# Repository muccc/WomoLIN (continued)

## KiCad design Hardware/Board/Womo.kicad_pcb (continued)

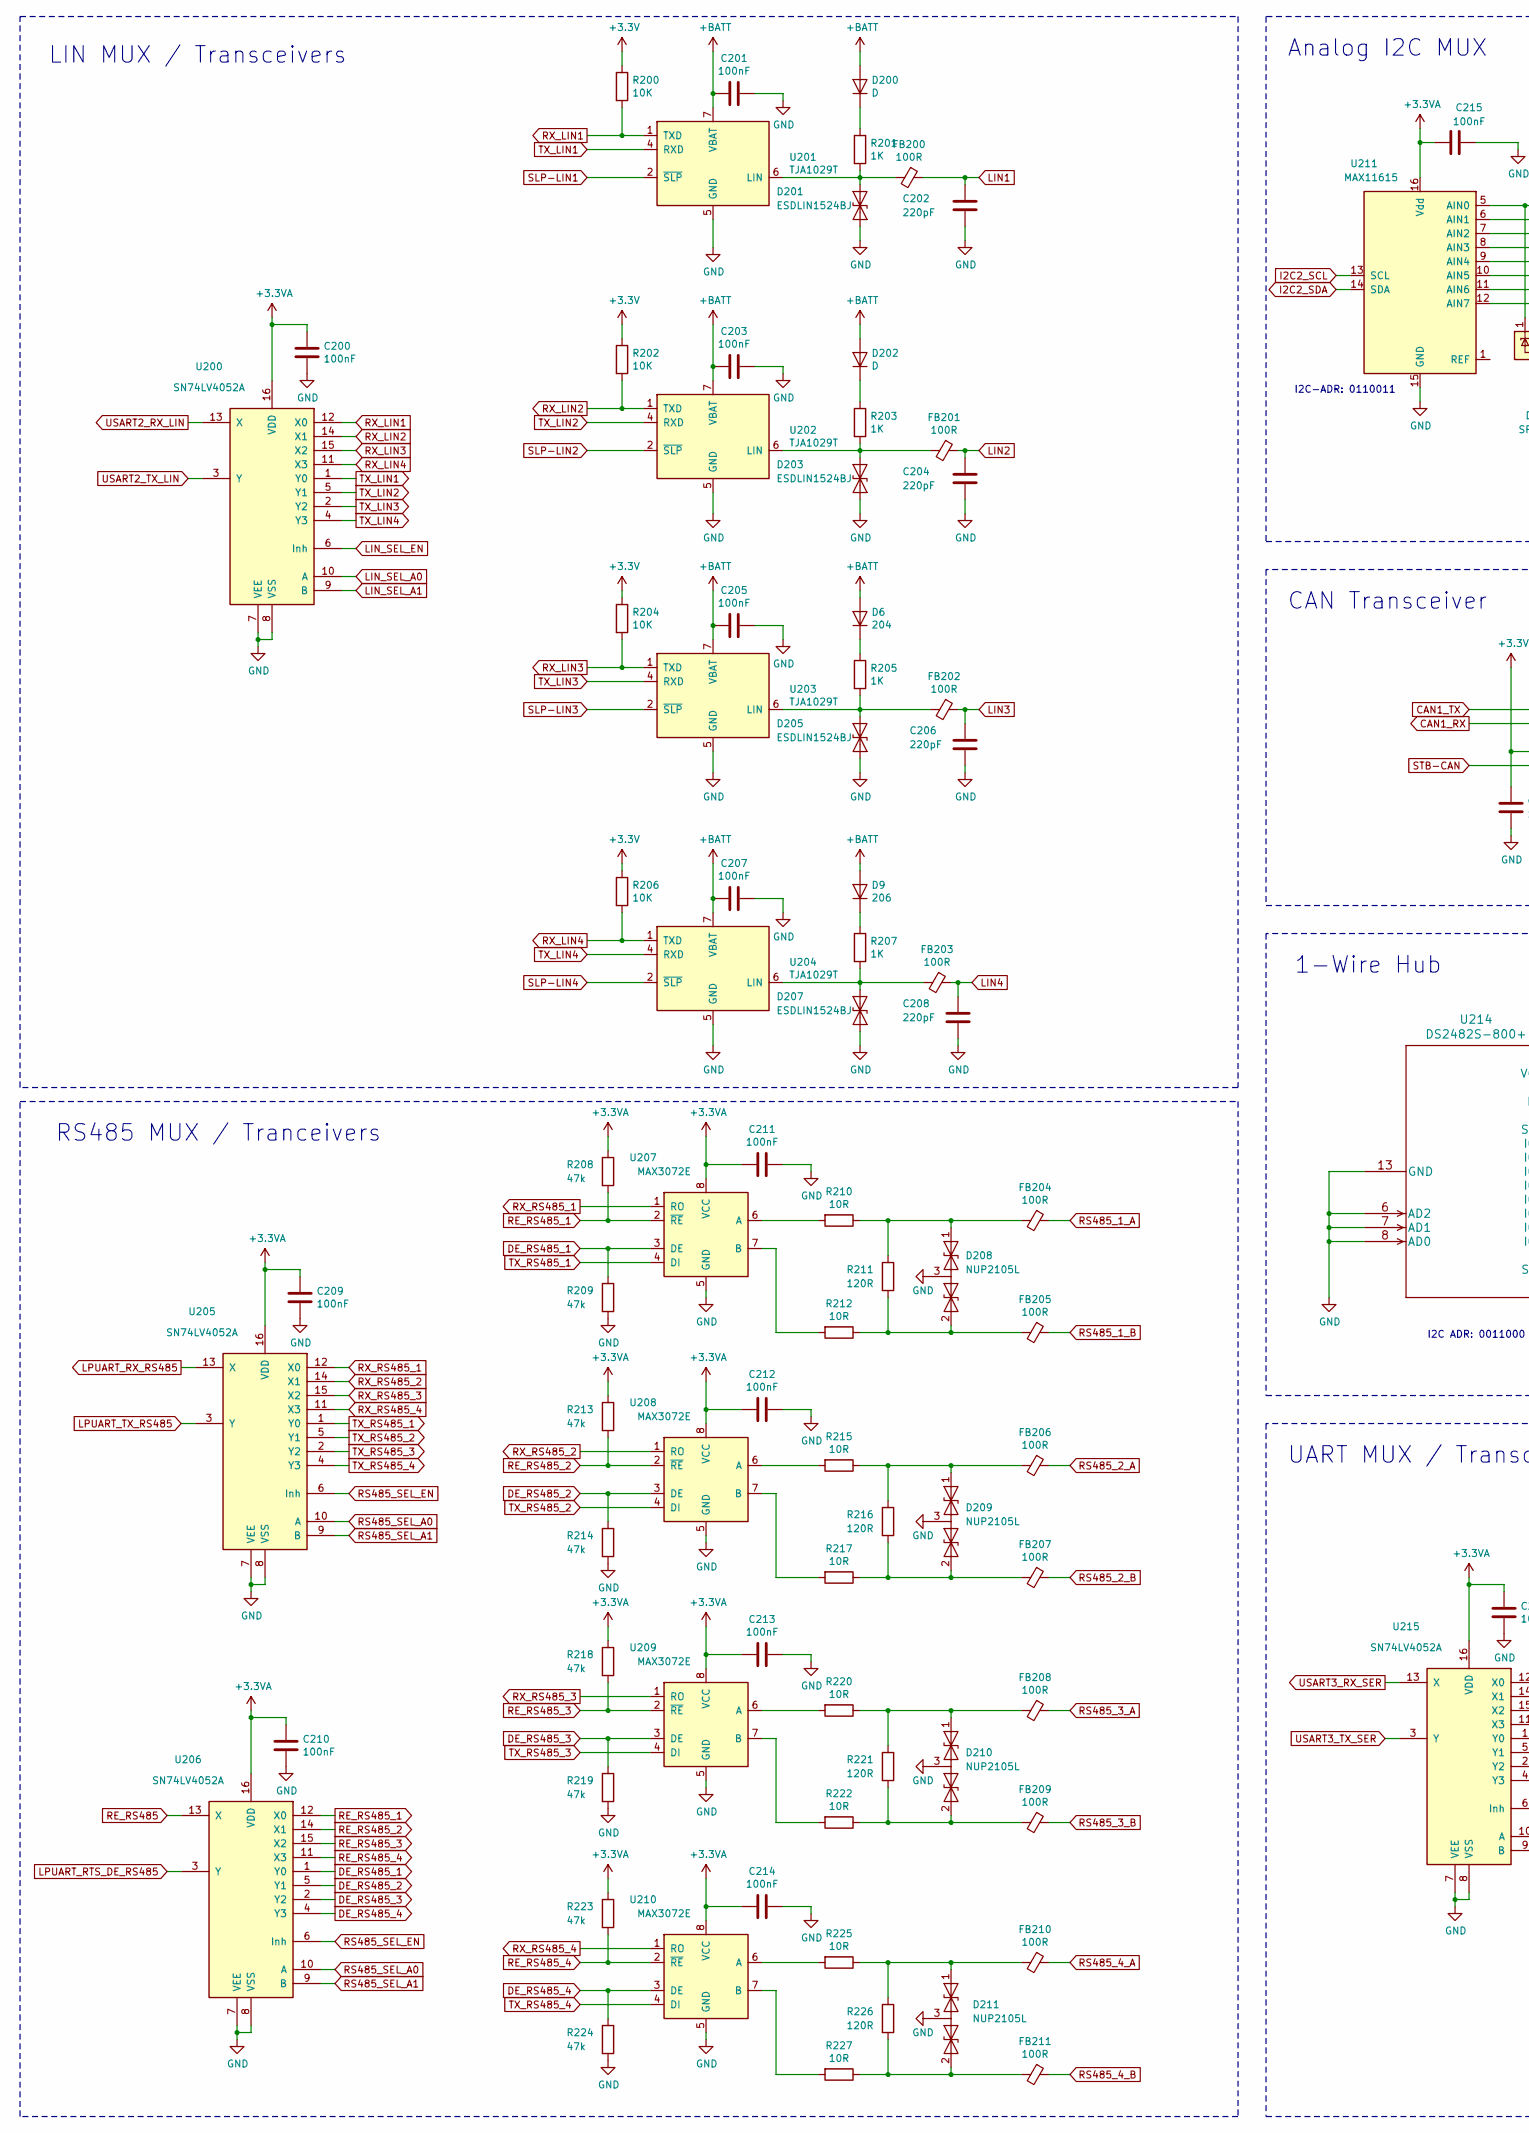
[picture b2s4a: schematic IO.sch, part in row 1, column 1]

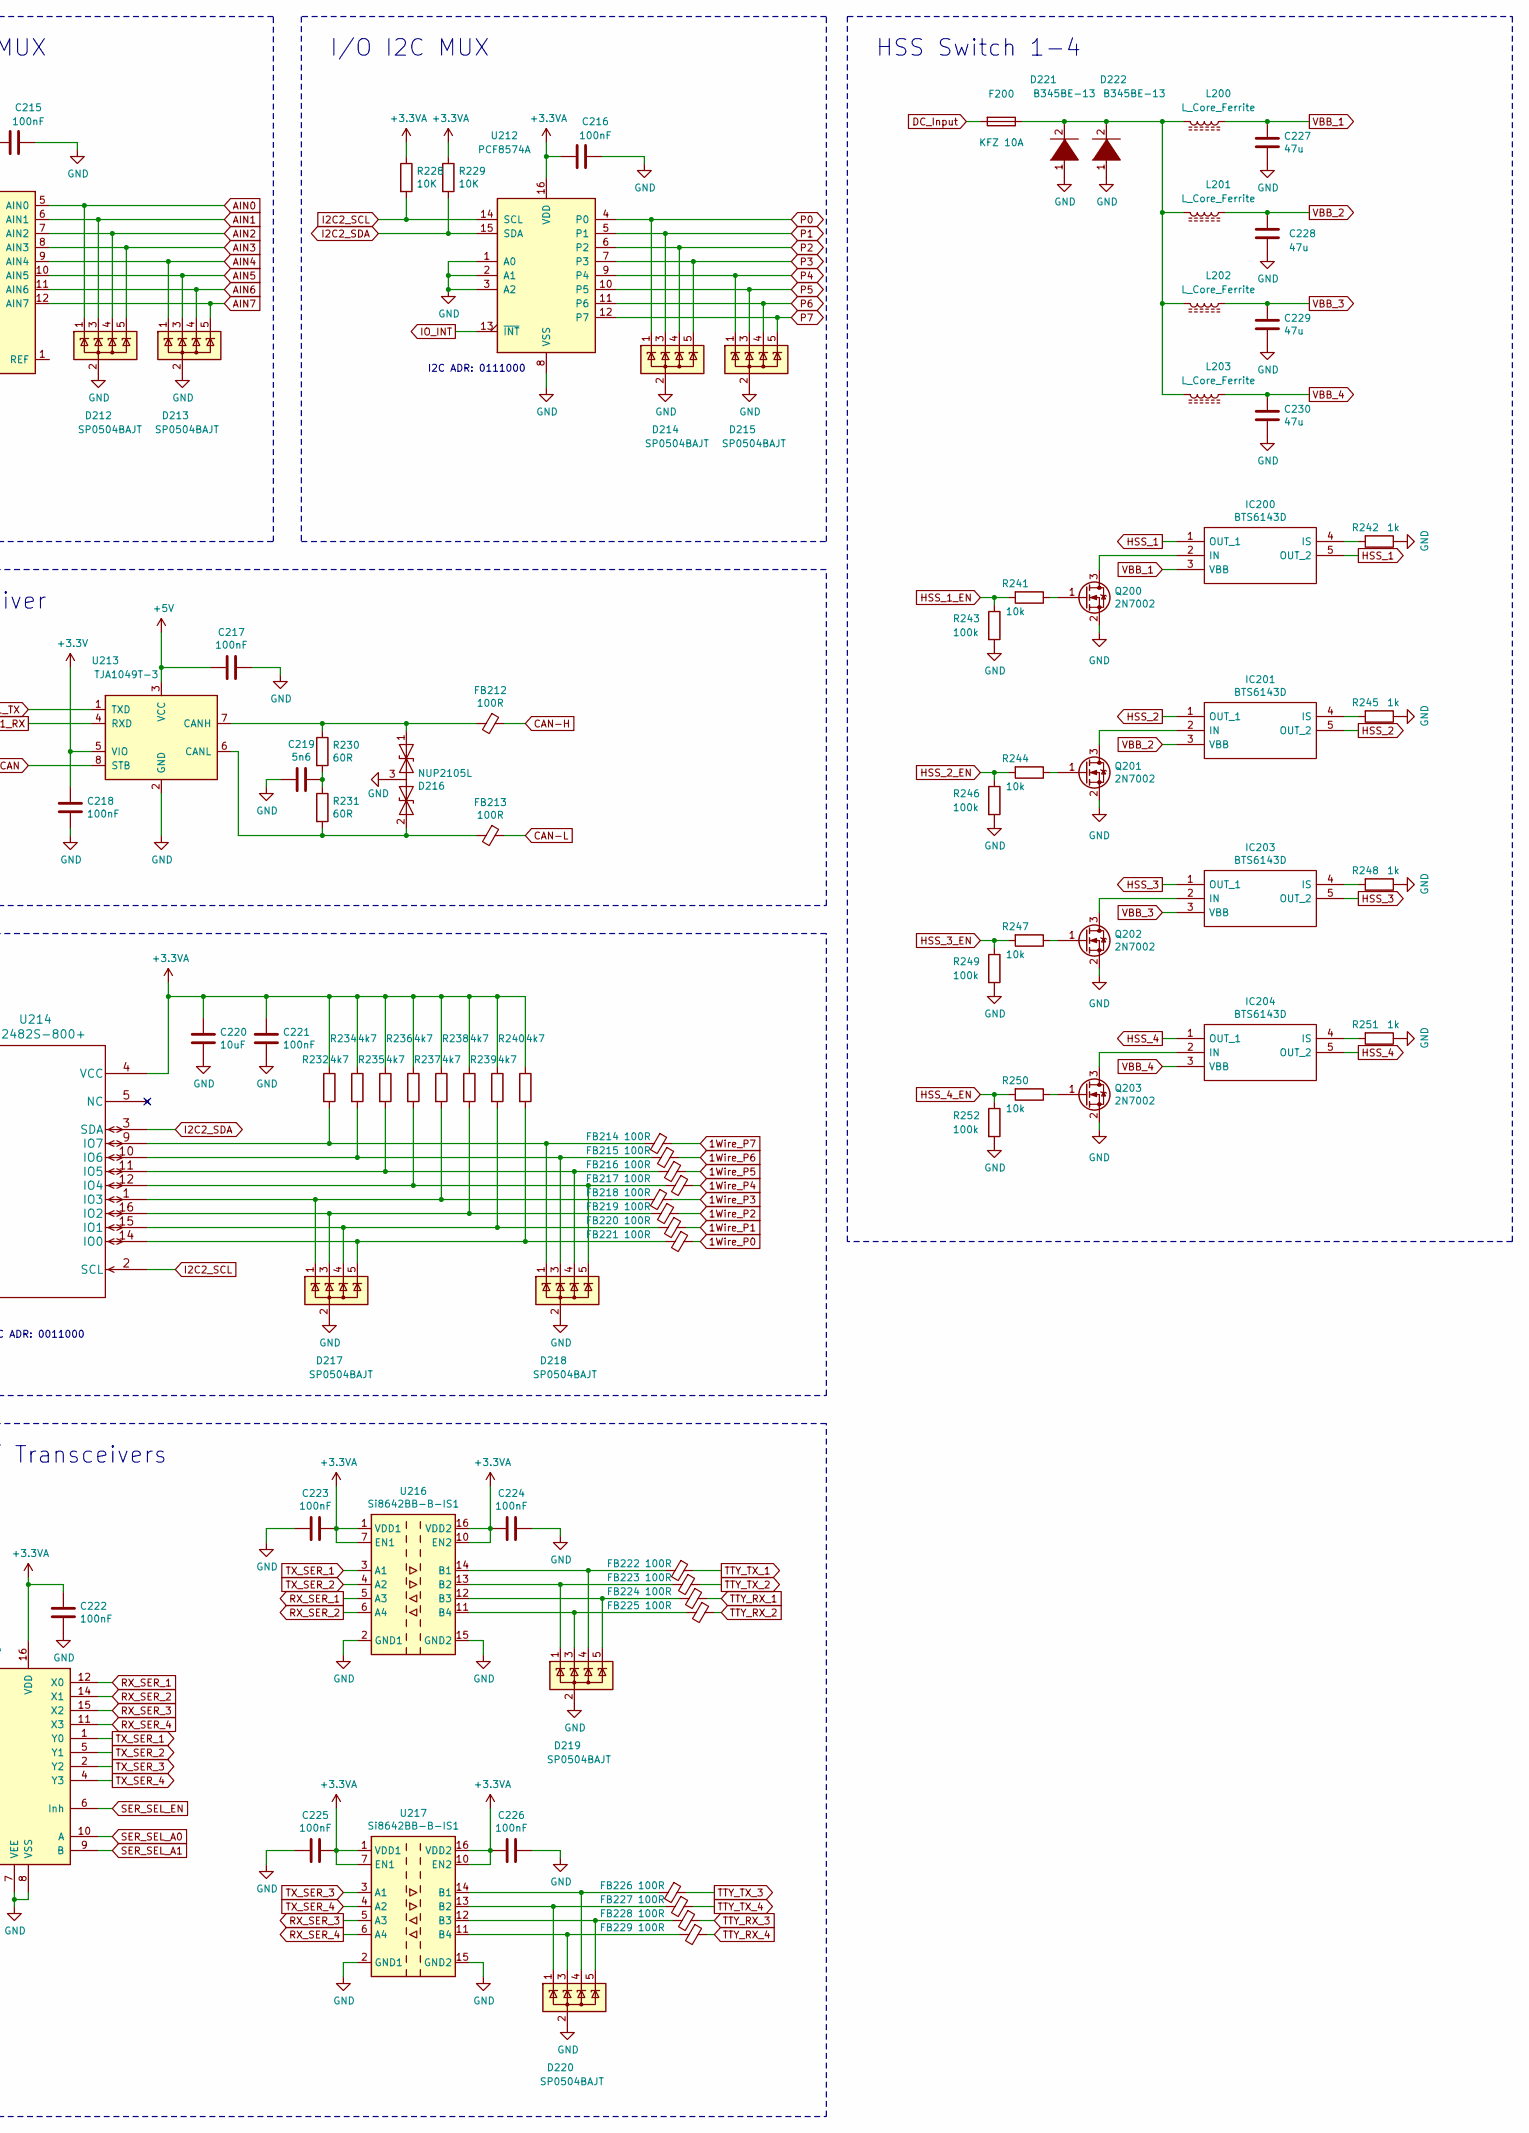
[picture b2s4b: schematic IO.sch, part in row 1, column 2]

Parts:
C200, C201, C203, C205, C207, C209, C210, C211, C212, C213, C214, C215, C216, C217, C218, C221, C222, C223, C224, C225, C226: 100nF; C_0603_1608Metric
C202, C204, C206, C208: 220pF; C_0603_1608Metric
C219: 5n6; C_0603_1608Metric
C220: 10uF; C_1210_3225Metric
C227, C228, C229, C230: 47u; C_1210_3225Metric
D6: 204; D_SOD-323
D9: 206; D_SOD-323
D200, D202: D; D_SOD-323
D201, D203, D205, D207: ESDLIN1524BJ; D_SOD-323
D208, D209, D210, D211, D216: NUP2105L; SOT-23
D212, D213, D214, D215, D217, D218, D219, D220: SP0504BAJT; SOT-353_SC-70-5
D221, D222: B345BE-13; D_SMB
F200: KFZ 10A; Fuseholder_Blade_ATO_Littelfuse_Pudenz_2_Pin
FB200, FB201, FB202, FB203, FB204, FB205, FB206, FB207, FB208, FB209, FB210, FB211, FB212, FB213, FB214, FB215, FB216, FB217, FB218, FB219, FB220, FB221, FB222, FB223, FB224, FB225, FB226, FB227, FB228, FB229: 100R; L_0603_1608Metric
IC200, IC201, IC203, IC204: BTS6143D; Mouser Part Number 726-BTS6143D
L200, L201, L202, L203: L_Core_Ferrite; L_Coilcraft_XxL4020
Q200, Q201, Q202, Q203: 2N7002; SOT-23
R200, R202, R204, R206, R228, R229: 10K; R_0603_1608Metric
R201, R203, R205, R207: 1K; R_0603_1608Metric
R208, R209, R213, R214, R218, R219, R223, R224: 47k; R_0603_1608Metric
R210, R212, R215, R217, R220, R222, R225, R227: 10R; R_0603_1608Metric
R211, R216, R221, R226: 120R; R_0603_1608Metric
R230, R231: 60R; R_0603_1608Metric
R232, R234, R235, R236, R237, R238, R239, R240: 4k7; R_0603_1608Metric
R241, R244, R247, R250: 10k; R_0603_1608Metric
R242, R245, R248, R251: 1k; R_0603_1608Metric
R243, R246, R249, R252: 100k; R_0603_1608Metric
U200, U205, U206, U215: SN74LV4052A; TSSOP-16_4.4x5mm_P0.65mm
U201, U202, U203, U204: TJA1029T; SOIC-8_3.9x4.9mm_P1.27mm
U207, U208, U209, U210: MAX3072E; SOIC-8_3.9x4.9mm_P1.27mm
U211: MAX11615; QSOP-16_3.9x4.9mm_P0.635mm
U212: PCF8574A; SOIC-16W_7.5x10.3mm_P1.27mm
U213: TJA1049T-3; SOIC-8_3.9x4.9mm_P1.27mm
U214: DS2482S-800+; SOIC-16_3.9x9.9mm_P1.27mm
U216, U217: Si8642BB-B-IS1; SOIC-16_3.9x9.9mm_P1.27mm

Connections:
1Wire_P0: FB221.1; also elsewhere on the board
1Wire_P1: FB220.1; also elsewhere on the board
1Wire_P2: FB219.1; also elsewhere on the board
1Wire_P3: FB218.1; also elsewhere on the board
1Wire_P4: FB217.1; also elsewhere on the board
1Wire_P5: FB216.1; also elsewhere on the board
1Wire_P6: FB215.1; also elsewhere on the board
1Wire_P7: FB214.1; also elsewhere on the board
+3.3VA: C200.1, C209.1, C210.1, C211.2, C212.2, C213.2, C214.2, C215.2, C216.2, C220.1, C221.1, C222.1, C223.1, C224.2, C225.1, C226.2, R208.1, R213.1, R218.1, R223.1, R228.1, R229.1, R232.1, R234.1, R235.1, R236.1, R237.1, R238.1, R239.1, R240.1, U200.16 (VDD), U205.16 (VDD), U206.16 (VDD), U207.8 (VCC), U208.8 (VCC), U209.8 (VCC), U210.8 (VCC), U211.16 (Vdd), U212.16 (VDD), U214.4 (VCC), U215.16 (VDD), U216.1 (VDD1), U216.7 (EN1), U216.10 (EN2), U216.16 (VDD2), U217.1 (VDD1), U217.7 (EN1), U217.10 (EN2), U217.16 (VDD2); also elsewhere on the board
+3V3: C218.1, R200.1, R202.1, R204.1, R206.1, U213.5 (VIO); also elsewhere on the board
+5V: C217.2, U213.3 (VCC); also elsewhere on the board
+BATT: C201.2, C203.2, C205.2, C207.2, D6.2 (A), D9.2 (A), D200.2 (A), D202.2 (A), U201.7 (VBAT), U202.7 (VBAT), U203.7 (VBAT), U204.7 (VBAT); also elsewhere on the board
AIN0: D212.1 (K), U211.5 (AIN0); also elsewhere on the board
AIN1: D212.3 (K), U211.6 (AIN1); also elsewhere on the board
AIN2: D212.4 (K), U211.7 (AIN2); also elsewhere on the board
AIN3: D212.5 (K), U211.8 (AIN3); also elsewhere on the board
AIN4: D213.1 (K), U211.9 (AIN4); also elsewhere on the board
AIN5: D213.3 (K), U211.10 (AIN5); also elsewhere on the board
AIN6: D213.4 (K), U211.11 (AIN6); also elsewhere on the board
AIN7: D213.5 (K), U211.12 (AIN7); also elsewhere on the board
CAN1_RX: U213.4 (RXD); also elsewhere on the board
CAN1_TX: U213.1 (TXD); also elsewhere on the board
CAN-H: FB212.1; also elsewhere on the board
CAN-L: FB213.1; also elsewhere on the board
DC_Input: F200.2; also elsewhere on the board
DE_RS485_1: R209.1, U206.1 (Y0), U207.3 (DE)
DE_RS485_2: R214.1, U206.5 (Y1), U208.3 (DE)
DE_RS485_3: R219.1, U206.2 (Y2), U209.3 (DE)
DE_RS485_4: R224.1, U206.4 (Y3), U210.3 (DE)
GND: C200.2, C201.1, C202.2, C203.1, C204.2, C205.1, C206.2, C207.1, C208.2, C209.2, C210.2, C211.1, C212.1, C213.1, C214.1, C215.1, C216.1, C217.1, C218.2, C219.2, C220.2, C221.2, C222.2, C223.2, C224.1, C225.2, C226.1, C227.2, C228.2, C229.2, C230.2, D201.2 (A2), D203.2 (A2), D205.2 (A2), D207.2 (A2), D208.3 (common), D209.3 (common), D210.3 (common), D211.3 (common), D212.2 (A), D213.2 (A), D214.2 (A), D215.2 (A), D216.3 (common), D217.2 (A), D218.2 (A), D219.2 (A), D220.2 (A), D221.1 (K), D222.1 (K), Q200.2 (S), Q201.2 (S), Q202.2 (S), Q203.2 (S), R209.2, R214.2, R219.2, R224.2, R242.1, R243.2, R245.1, R246.2, R248.1, R249.2, R251.1, R252.2, U200.7 (VEE), U200.8 (VSS), U201.5 (GND), U202.5 (GND), U203.5 (GND), U204.5 (GND), U205.7 (VEE), U205.8 (VSS), U206.7 (VEE), U206.8 (VSS), U207.5 (GND), U208.5 (GND), U209.5 (GND), U210.5 (GND), U211.15 (GND), U212.1 (A0), U212.2 (A1), U212.3 (A2), U212.8 (VSS), U213.2 (GND), U214.6 (AD2), U214.7 (AD1), U214.8 (AD0), U214.13 (GND), U215.7 (VEE), U215.8 (VSS), U216.2 (GND1), U216.8 (GND1), U216.9 (GND2), U216.15 (GND2), U217.2 (GND1), U217.8 (GND1), U217.9 (GND2), U217.15 (GND2); also elsewhere on the board
HSS_1: IC200.1 (OUT_1), IC200.5 (OUT_2); also elsewhere on the board
HSS_1_EN: R241.2, R243.1; also elsewhere on the board
HSS_2: IC201.1 (OUT_1), IC201.5 (OUT_2); also elsewhere on the board
HSS_2_EN: R244.2, R246.1; also elsewhere on the board
HSS_3: IC203.1 (OUT_1), IC203.5 (OUT_2); also elsewhere on the board
HSS_3_EN: R247.2, R249.1; also elsewhere on the board
HSS_4: IC204.1 (OUT_1), IC204.5 (OUT_2); also elsewhere on the board
HSS_4_EN: R250.2, R252.1; also elsewhere on the board
I2C2_SCL: R228.2, U211.13 (SCL), U212.14 (SCL), U214.2 (SCL); also elsewhere on the board
I2C2_SDA: R229.2, U211.14 (SDA), U212.15 (SDA), U214.3 (SDA); also elsewhere on the board
IO_INT: U212.13 (~INT~); also elsewhere on the board
LIN1: C202.1, FB200.1; also elsewhere on the board
LIN2: C204.1, FB201.1; also elsewhere on the board
LIN3: C206.1, FB202.1; also elsewhere on the board
LIN4: C208.1, FB203.1; also elsewhere on the board
LIN_SEL_A0: U200.10 (A); also elsewhere on the board
LIN_SEL_A1: U200.9 (B); also elsewhere on the board
LIN_SEL_EN: U200.6 (Inh); also elsewhere on the board
LPUART_RTS_DE_RS485: U206.3 (Y); also elsewhere on the board
LPUART_RX_RS485: U205.13 (X); also elsewhere on the board
LPUART_TX_RS485: U205.3 (Y); also elsewhere on the board
unnamed: C219.1, R230.2, R231.1
unnamed: D6.1 (K), R205.1
unnamed: D9.1 (K), R207.1
unnamed: D200.1 (K), R201.1
unnamed: D201.1 (A1), FB200.2, R201.2, U201.6 (LIN)
unnamed: D202.1 (K), R203.1
unnamed: D203.1 (A1), FB201.2, R203.2, U202.6 (LIN)
unnamed: D205.1 (A1), FB202.2, R205.2, U203.6 (LIN)
unnamed: D207.1 (A1), FB203.2, R207.2, U204.6 (LIN)
unnamed: D208.1 (A1), FB204.2, R210.1, R211.1
unnamed: D208.2 (A2), FB205.2, R211.2, R212.1
unnamed: D209.1 (A1), FB206.2, R215.1, R216.1
unnamed: D209.2 (A2), FB207.2, R216.2, R217.1
unnamed: D210.1 (A1), FB208.2, R220.1, R221.1
unnamed: D210.2 (A2), FB209.2, R221.2, R222.1
unnamed: D211.1 (A1), FB210.2, R225.1, R226.1
unnamed: D211.2 (A2), FB211.2, R226.2, R227.1
unnamed: D216.1 (A1), FB212.2, R230.1, U213.7 (CANH)
unnamed: D216.2 (A2), FB213.2, R231.2, U213.6 (CANL)
unnamed: D217.1 (K), FB218.2, R237.2, U214.1 (IO3)
unnamed: D217.3 (K), FB219.2, R238.2, U214.16 (IO2)
unnamed: D217.4 (K), FB220.2, R239.2, U214.15 (IO1)
unnamed: D217.5 (K), FB221.2, R240.2, U214.14 (IO0)
unnamed: D218.1 (K), FB214.2, R232.2, U214.9 (IO7)
unnamed: D218.3 (K), FB215.2, R234.2, U214.10 (IO6)
unnamed: D218.4 (K), FB216.2, R235.2, U214.11 (IO5)
unnamed: D218.5 (K), FB217.2, R236.2, U214.12 (IO4)
unnamed: D219.1 (K), FB223.2, U216.13 (B2)
unnamed: D219.3 (K), FB225.2, U216.11 (B4)
unnamed: D219.4 (K), FB222.2, U216.14 (B1)
unnamed: D219.5 (K), FB224.2, U216.12 (B3)
unnamed: D220.1 (K), FB227.2, U217.13 (B2)
unnamed: D220.3 (K), FB229.2, U217.11 (B4)
unnamed: D220.4 (K), FB226.2, U217.14 (B1)
unnamed: D220.5 (K), FB228.2, U217.12 (B3)
unnamed: D221.2 (A), D222.2 (A), F200.1, L200.2, L201.2, L202.2, L203.2
unnamed: IC200.2 (IN), Q200.3 (D)
unnamed: IC200.4 (IS), R242.2
unnamed: IC201.2 (IN), Q201.3 (D)
unnamed: IC201.4 (IS), R245.2
unnamed: IC203.2 (IN), Q202.3 (D)
unnamed: IC203.4 (IS), R248.2
unnamed: IC204.2 (IN), Q203.3 (D)
unnamed: IC204.4 (IS), R251.2
unnamed: Q200.1 (G), R241.1
unnamed: Q201.1 (G), R244.1
unnamed: Q202.1 (G), R247.1
unnamed: Q203.1 (G), R250.1
unnamed: R210.2, U207.6 (A)
unnamed: R212.2, U207.7 (B)
unnamed: R215.2, U208.6 (A)
unnamed: R217.2, U208.7 (B)
unnamed: R220.2, U209.6 (A)
unnamed: R222.2, U209.7 (B)
unnamed: R225.2, U210.6 (A)
unnamed: R227.2, U210.7 (B)
P0: D214.1 (K), U212.4 (P0); also elsewhere on the board
P1: D214.3 (K), U212.5 (P1); also elsewhere on the board
P2: D214.4 (K), U212.6 (P2); also elsewhere on the board
P3: D214.5 (K), U212.7 (P3); also elsewhere on the board
P4: D215.1 (K), U212.9 (P4); also elsewhere on the board
P5: D215.3 (K), U212.10 (P5); also elsewhere on the board
P6: D215.4 (K), U212.11 (P6); also elsewhere on the board
P7: D215.5 (K), U212.12 (P7); also elsewhere on the board
RE_RS485: U206.13 (X); also elsewhere on the board
RE_RS485_1: R208.2, U206.12 (X0), U207.2 (~RE~)
RE_RS485_2: R213.2, U206.14 (X1), U208.2 (~RE~)
RE_RS485_3: R218.2, U206.15 (X2), U209.2 (~RE~)
RE_RS485_4: R223.2, U206.11 (X3), U210.2 (~RE~)
RS485_1_A: FB204.1; also elsewhere on the board
RS485_1_B: FB205.1; also elsewhere on the board
RS485_2_A: FB206.1; also elsewhere on the board
RS485_2_B: FB207.1; also elsewhere on the board
RS485_3_A: FB208.1; also elsewhere on the board
RS485_3_B: FB209.1; also elsewhere on the board
RS485_4_A: FB210.1; also elsewhere on the board
RS485_4_B: FB211.1; also elsewhere on the board
RS485_SEL_A0: U205.10 (A), U206.10 (A); also elsewhere on the board
RS485_SEL_A1: U205.9 (B), U206.9 (B); also elsewhere on the board
RS485_SEL_EN: U205.6 (Inh), U206.6 (Inh); also elsewhere on the board
RX_LIN1: R200.2, U200.12 (X0), U201.1 (TXD)
RX_LIN2: R202.2, U200.14 (X1), U202.1 (TXD)
RX_LIN3: R204.2, U200.15 (X2), U203.1 (TXD)
RX_LIN4: R206.2, U200.11 (X3), U204.1 (TXD)
RX_RS485_1: U205.12 (X0), U207.1 (RO)
RX_RS485_2: U205.14 (X1), U208.1 (RO)
RX_RS485_3: U205.15 (X2), U209.1 (RO)
RX_RS485_4: U205.11 (X3), U210.1 (RO)
RX_SER_1: U215.12 (X0), U216.5 (A3)
RX_SER_2: U215.14 (X1), U216.6 (A4)
RX_SER_3: U215.15 (X2), U217.5 (A3)
RX_SER_4: U215.11 (X3), U217.6 (A4)
SER_SEL_A0: U215.10 (A); also elsewhere on the board
SER_SEL_A1: U215.9 (B); also elsewhere on the board
SER_SEL_EN: U215.6 (Inh); also elsewhere on the board
SLP-LIN1: U201.2 (~SLP~); also elsewhere on the board
SLP-LIN2: U202.2 (~SLP~); also elsewhere on the board
SLP-LIN3: U203.2 (~SLP~); also elsewhere on the board
SLP-LIN4: U204.2 (~SLP~); also elsewhere on the board
STB-CAN: U213.8 (STB); also elsewhere on the board
TTY_RX_1: FB224.1; also elsewhere on the board
TTY_RX_2: FB225.1; also elsewhere on the board
TTY_RX_3: FB228.1; also elsewhere on the board
TTY_RX_4: FB229.1; also elsewhere on the board
TTY_TX_1: FB222.1; also elsewhere on the board
TTY_TX_2: FB223.1; also elsewhere on the board
TTY_TX_3: FB226.1; also elsewhere on the board
TTY_TX_4: FB227.1; also elsewhere on the board
TX_LIN1: U200.1 (Y0), U201.4 (RXD)
TX_LIN2: U200.5 (Y1), U202.4 (RXD)
TX_LIN3: U200.2 (Y2), U203.4 (RXD)
TX_LIN4: U200.4 (Y3), U204.4 (RXD)
TX_RS485_1: U205.1 (Y0), U207.4 (DI)
TX_RS485_2: U205.5 (Y1), U208.4 (DI)
TX_RS485_3: U205.2 (Y2), U209.4 (DI)
TX_RS485_4: U205.4 (Y3), U210.4 (DI)
TX_SER_1: U215.1 (Y0), U216.3 (A1)
TX_SER_2: U215.5 (Y1), U216.4 (A2)
TX_SER_3: U215.2 (Y2), U217.3 (A1)
TX_SER_4: U215.4 (Y3), U217.4 (A2)
USART2_RX_LIN: U200.13 (X); also elsewhere on the board
USART2_TX_LIN: U200.3 (Y); also elsewhere on the board
USART3_RX_SER: U215.13 (X); also elsewhere on the board
USART3_TX_SER: U215.3 (Y); also elsewhere on the board
VBB_1: C227.1, IC200.3 (VBB), L200.1
VBB_2: C228.1, IC201.3 (VBB), L201.1
VBB_3: C229.1, IC203.3 (VBB), L202.1
VBB_4: C230.1, IC204.3 (VBB), L203.1

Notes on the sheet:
I2C-ADR: 0110011
I2C ADR: 0111000
I2C ADR: 0011000
LIN MUX / Transceivers
RS485 MUX / Tranceivers
UART MUX / Transceivers
CAN Transceiver
1-Wire Hub
Analog I2C MUX
I/O I2C MUX
HSS Switch 1-4

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
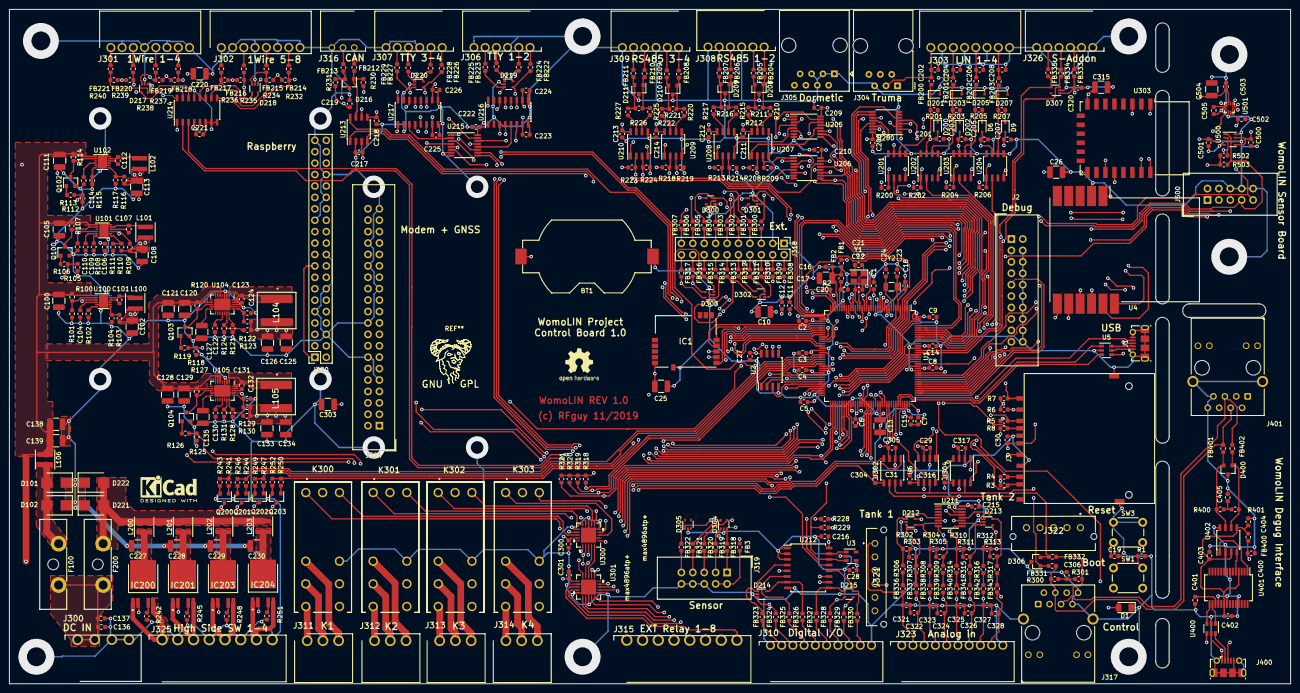
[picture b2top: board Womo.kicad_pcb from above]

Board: 4 copper layers, 285.0 x 150.0 mm, 465 parts (0 on the bottom side), 417 nets.

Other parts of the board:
C132: 100nF; C_0603_1608Metric
C133, C134: 22uF; C_1210_3225Metric
C135: 10u; C_1210_3225Metric
C136: 100n; C_0603_1608Metric
C137: 1u; C_0603_1608Metric
C138, C139: 47u; C_1210_3225Metric
F100: KFZ 5A; Fuseholder_Blade_ATO_Littelfuse_Pudenz_2_Pin
L106: L_Core_Ferrite; L_Coilcraft_XxL4020
Q104: 2N7002; SOT-23
R116: 86k6; R_0603_1608Metric
R117: 32k4; R_0603_1608Metric
R118, R125: 100k; R_0603_1608Metric
R126: 10k; R_0603_1608Metric
R127: 40k2; R_0603_1608Metric
R128: 49k9; R_0603_1608Metric
R129: 4r7; R_0603_1608Metric
R130: 105k; R_0603_1608Metric
R131: 22k6; R_0603_1608Metric
U105: MAX17574; QFN-24-1EP_4x5mm_P0.5mm_EP2.65x3.65mm

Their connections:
5V_GSM_EN: R125.1, R126.2; also elsewhere on the board
5V_Raspi_EN: R118.1; also elsewhere on the board
+3.3VA: R116.1; also elsewhere on the board
+5VL: C133.1, C134.1, R129.1, R130.1; also elsewhere on the board
+BATT: C138.1, C139.1, L106.1, R127.1, U105.5, U105.6, U105.7, U105.9; also elsewhere on the board
DC_Input: C136.1, C137.1, F100.2; also elsewhere on the board
GND: C132.2, C133.2, C134.2, C135.1, C136.2, C137.2, C138.2, C139.2, Q104.2, R117.2, R118.2, R125.2, R128.2, R131.2, U105.2, U105.3, U105.11, U105.21, U105.25; also elsewhere on the board
unnamed 125: U105.16; also elsewhere on the board
unnamed 126: U105.1, U105.23, U105.24; also elsewhere on the board
unnamed 127: U105.22; also elsewhere on the board
unnamed: C132.1, R129.2, U105.20
unnamed: C135.2, U105.12
unnamed 148: F100.1, L106.2; also elsewhere on the board
unnamed: Q104.1, R126.1
unnamed: Q104.3, R127.2, U105.10
unnamed 346: R116.2, R117.1; also elsewhere on the board
unnamed: R128.1, U105.19
unnamed: R130.2, R131.1, U105.18

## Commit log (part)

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2018-10-13 Create Log Truma CP Plus init mit AC
    Log file mit Truma CP Plus Bedienteil was init mit AC Aventis pro macht
2018-10-13 Create Log Truma CP Plus init mit Combi 6
    Truma CP Plus Bedienteil was Init mit der Compi 6 Heizung macht
2018-10-13 Create Log Truma CP Plus init mit Combi 6 und AC
    Log File init mit Bedienteil Truma CP plus, einer einer Combi 6 und Aventis pro AC, viel Trafic hinterher
2018-10-31 Update Log Truma CP Plus init mit AC
    Add Speed and Bus TIN Port
2018-10-31 Update Log Truma CP Plus init mit Combi 6
2018-10-31 Update Log Truma CP Plus init mit Combi 6 und AC
2018-10-31 Update README.md
    Warnung ins Readme
2018-10-31 Update README.md
    Anschluss Info hinzu
2019-02-17 add logs
2019-03-15 KiCad Schematic angelegt, Prozessor und Interface Bausteine ausgewählt.
2019-03-27 Businterface Schaltplan und Datasheets hinzu gefügt
2019-03-29 Controller auf 100 Pin Version geändert, Pins ersten Funktionen zugeordnet.
2019-04-01 JTAG und USB Anschlüsse zugefügt
2019-04-04 Schaltregler Design fertig gestellt, Datenblätter hinzu gefügt.
2019-04-05 FTDI EVE Touch hinzugefügt
2019-04-12 1Wire Power Pull Up. ESP Modul added
2019-04-16 Wago und FPC Libs zugefügt
2019-04-17 Netzliste und Board erstellt, hier sind noch Fehler im Bereich Footprints, BLE Modul nRF8001 hinzugefügt, erste Anschlussklemmen zugefügt
2019-04-22 Easterhegg Vortrag hinzu gefügt
2019-04-26 Änderung CPU auf einen mit Display Controller, vorbereitung zum Anschluss SSD1963 und Digital RGB Displays
2019-05-10 Display auf 40 Pin FPC reduziert, nur Verwendung des internen Display Controllers, Library Updates
2019-05-28 Octo SPI Flash und RAM zugefügt, weitere Bezeichnungen auf Stand gebracht
2019-05-31 Eine Menge Arbeit auf der GPN, fast fertig im Schaltplan.
2019-05-31 GPN Arbeit
2019-06-11 Board to Board Verbindung eingefügt
2019-06-12 Resitiven Touch Controller eingefügt, diverse I2C Parts hinzu gefügt, Netze umgenannt
2019-06-13 GSM Modul SIM800L eingefügt, Spannung MCU Board umgenannt
2019-06-14 MCU Section fertig, Analog Inputs angelegt, Schaltplan neu organisiert, alte Datenblätter entfernt.
2019-06-27 Trennung MCU und Rest, Footprints fast alles zugewiesen, GSM Modul integriert, viel Kleinkram
2019-06-28 Footprints zuweisungen
2019-07-02 Alle Footprints definiert, Libs angepasst, Layout gestartet mit Plazierung, Controller und Breakout Netzmäßig getrennt.
2019-07-03 Komplete enummerierung Geändert, Schaltplan zusammengefasst, Layout nochmals reset. BOM zu 75% fertig gestellt
2019-07-05 BOM für Mouser fertig gestellt.
2019-07-11 Bauteil Gruppierungen im Layout
2019-09-19 Änderung des Konzeptes auf 2 Boards, eines TFT Touch mit STM32L4R9, das rein die Bedienung macht. Control Board mit STM32L476, mit noch mehr Schnittstellen. Bus zwischen Display, Board, Raspberry/ESP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
2019-09-19 added system applikation und benutzerschnittstellen jeweils version 1.0
2019-09-19 added gui display unit freeplan
2019-09-22 added dia hardware-controlbus version 1.0
2019-09-26 Display Unit Lib Fehler behoben, und noch Zeug raus geworfen Library jetzt projekt spezifisch im Hardware root.. Hauptplatine rund um den Prozessor a bissl was getan, vorbereitung Quadspi Flash und S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
2019-09-27 Alle Busse aus dem Prozessor geroutet, Multplexing der LIN, RS485 und TTY Busse, diverse Aufräumarbeiten.
2019-09-28 added first pc gui
2019-10-01 Prozessor Pins zugeordnet, 4 bistabile Relais, CAN Control Interface, CAN Debug Adapter, Lagesensor zugefügt, Umwelt Sensor, ISM 868 MHz Tranceiver, ESP and Control Bus. UID Eprom. Etliche Aufräum Ar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
2019-10-02 Lib Update, Relais Treiber hinzugefügt, Kleinkram
2019-10-02 Vorher Speichern hilft
2019-10-03 added signals.xml
2019-10-04 Wago Steckverbinder hinzugefügt, Schaltplan erheblich aufgeräumt, Funktionsgruppen bezeichnet, Extension Port (Port PF) als Stecker hinzu gefügt
2019-10-04 added first version of Readme and Dockerfile
2019-10-04 test add image to readme
2019-10-04 test image to readme
2019-10-04 added image benutzerschnittstellen to readme and test link to latest
2019-10-04 image link dont work within readme
2019-10-05 Dockerfile modified
2019-10-06 docker stuff and renamend doc to Doc
2019-10-06 docker stuff added kicad to docker
2019-10-08 modified README
2019-10-08 added xml units
2019-10-14 Schaltplan erst mal fertig gestellt, Bilblotheken angepasst, High Side Treiber zugefügt
2019-10-15 added Projektbeschreibung
2019-10-16 Schaltplan: Pulldown bei den Mosfets zugefügt, Fehler Korrektur, Baulteil Footprints zugewiesen und Lib angepasst, Netztliste ohne Fehler zum Layout übertragbar. Board: Auf neues Design angepasst, Be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
2019-10-17 Schaltplan: Kleinere Korrekturen Layout: I/O Ports Gröstenteils platziert
2019-10-18 Grobplatzierung abgeschlossen, Raspberry und GSM/GNSS Bohrungen Platziert, Befestigungsbohrungen festgelegt, Board Outline festgelegt
2019-10-19 Hardware Beschreibung ergänzt
2019-10-22 added docker for gcc 9
2019-10-24 added docker openjre11
2019-10-24 added docker eclipse
2019-10-27 added dockerfiles and myfr test programm
2019-10-27 docker stuff, add ignore for dot files and little changes on myfr test software
2019-10-27 added first version of uml diagram for sigunits, modified myfr test main
2019-10-28 Daten für Vortrag 36c3 ergänzt
2019-11-01 backup myfr stuff
2019-11-01 added myfr first prj structure
2019-11-01 added myfr readme file, added unittest in cmake file
2019-11-01 added birelay software design
2019-11-06 Kleinkram Layout
2019-11-12 Layout Arbeit, Project Library sollte jetzt auf allen Rechnern funktionieren. Leerzeichen entfernt.
2019-11-12 Ein paar Sachen vergessen
2019-11-14 Zwischenstand Layout, etliche Fehler im Schaltplan gefixt.
2019-11-15 Fehlende Masse Abblockung CPU, Anfang Prozessor Routing
2019-11-16 Rechte Seite CPU gerouted, SPI 1 / 2 getauscht.
2019-11-18 CPU Layout, Fehlerkorrektur
2019-11-19 CPU Routing komplett
2019-11-19 vergessen
2019-11-21 Masse und Power Flächen gerouted, bis auf Tochterboards alles komplett gerouted
2019-11-23 Layout abgeschlossen, DRC durch geführt, V1.0 fertig zum review
2019-11-24 Displayunit: Fix Libs, fix, Footprints, PCB angelegt, Auf eine Schaltplanseite reduziert.
2019-11-24 BOM erstellt, Fehler in Bauteilbezeichnung gefixt
2019-11-26 Fix Womo BRD für Produktion, Displayboard Schaltplan weitere Arbeiten.
2019-11-27 Fix: Produktionsdaten Board Arbeiten Schaltplan Displayunit
2019-12-02 Display Board kleinere Schaltplan Anpassung , Board Design an New Heaven Display angepasst, Platzierung zu 95 % abgeschlossen
2019-12-02 Displayboard: etwas Layout am Powersupply
2019-12-06 Displayunit: Zweite Controlbus Buchse hinzugefügt.
2019-12-06 Displayboard: Flex Stecker Position festgelegt, verschiebung von Componenten.
2019-12-07 added g++-8 to simulation build process
2019-12-07 cleanup
2019-12-07 added manager, serial, protocol
2019-12-09 Displayboard: Layout
2019-12-09 backup
2019-12-10 backup software design
2019-12-11 added first enums
2019-12-11 new compiler gcc9, update sources
2019-12-12 changed relay to inputoutput
2019-12-12 update sources
2019-12-12 software updates
2019-12-13 software change class names
2019-12-13 first sw version of mainunit simulation with 4 birelays
2019-12-16 include cmake build process
2019-12-16 added GPL3 licence to all files
2019-12-16 removed cout prints
2019-12-16 little code optimizations
2019-12-17 cleanup sources
2019-12-17 simulation always implemented
2019-12-17 update toolchain
2019-12-17 cleanup code
2019-12-19 backup integration version
2019-12-20 first version add git infos to fwversion
2019-12-20 backup getgitinfos.sh
2019-12-20 backup set version string
2019-12-20 update fw version
2019-12-20 added hw board infos
2019-12-21 removed empty xml folder and myfr folder
2019-12-30 added gimp files for videos and arm-g++-8
2020-01-07 Fix: behinderten Masse Bug an 3v3 Regler Mainunit und Displayboard
2020-01-23 added presentation 24.01.2020 Softwarekonzept
2020-02-11 Weitere Arbeiten am Layout, UID i2c Eeprom hinzugefügt.
2020-02-21 Displayboard fertig layoutet, kleinere Fehler beseitigt, WomoLin Biblothek senkrechter Würth RJ 45 zugefügt
2020-02-25 Commit Foo beseitigt, Änderung auf Displayboard auf Protofertiger Teile.
2020-03-07 Änderung PSU Displayboard, Lib angepast.
2020-03-18 PCB Prototypen Produktions Stand
2020-04-02 Display Board: Fix JTAG REF, LED Treiber > TPS61165, Spulen zurück auf XAL4040 Footprint, Auf Version 2.0 gehoben
2020-04-05 Kleinere Änderungen, aufgrund von Kicad Problemen, auf anderem System weiter arbeiten.
2020-04-07 SI8422 Lib angelegt, TTLRS232 einzeln isoliert, Victron VE Bus kompatieble Stecker zugefügt.
2020-04-15 Fix Lib gedrehte FPC Stecker, 10 Pin FPC hinzu gefügt (Buydisplay.com Alternative) Displayboard RS485 und CAN Option hinzu. Beginn Änderung Layout.
2020-04-16 Fix Womolin Lib, ein paar Bauteile fehlte Lötstopmaske. Displayboard stand zweite Prototyp Bestellung.
2020-04-21 Sunlord Spulen Footprint zugefügt
2020-04-22 Board: CAN auf 3V umgestellt, neue CAN Treiber, alle auf 3v3 CPU Power, Standby mit Pulll down, ohne PI und ESP keine Blockade des Busses, Schaltbare Abschlüsse vom CAN, Layout Arbeit.
2020-04-24 Board: Änderung Footprints, Debug geroutet, Beginn Platzierung Netzteil, Bezeichnungen und Werte aufgeräumt.
2020-04-24 Board: PSU platziert, Fehlerkorrektur, Routing PSU
2020-04-25 added Baseboard folder
2020-04-26 upgrade arm compiler to none-eabi-9-2019-q4
2020-04-28 Board: Grundsätzlich alles platziert, gerouted, DRC und Nacharbeiten fehlen noch.
2020-04-28 renamed Baseboard to Mainunit, dockerfile stuff
2020-04-28 Board: Power LED hinzu gefügt, Layout 99% fertig
2020-04-29 added new eclipse version to docker
2020-04-29 cleanup clean.sh script
2020-04-29 added strip command for release versions
2020-04-29 added arm building for mainunit
2020-04-29 added ifdef to serial_simulation_network
2020-04-29 added ifdef to serial
2020-04-30 updated dockefile kicad
2020-04-30 added GNU MCU to build eclipse
2020-04-30 Board: DRC Leiterbahn gefixt.
2020-05-02 Board: Partlist erstellt.
2020-05-03 new test version of a new software and build structure
2020-05-03 Board: Partlist mit Mouser und LCSC Partnummer erzeugt, kleiner Änderungen in der Bestückung, Änderung Womo Lib, Daten zur Anfrage an PCBAstore erzeugt.
2020-05-07 added cleanup stuff to build gcc dockerfile
2020-05-14 Add driver source code.
2020-05-16 added script clean docker
2020-05-16 Add driver cmake file.
2020-05-16 Add cmake for cmsis.
2020-05-16 Add cmake for hal.
2020-05-17 removed CMake build artifacts
2020-05-17 firmware/helper/build.sh creates binaries now outside of repo within directory build_womolin parallel to WomoLIN
2020-05-17 removed entry build within gitignore file
2020-05-19 Add driver hal cmsis libs to main target.
2020-05-19 Add startup code and linker script.
2020-05-20 cleanup CMake
2020-05-20 CMake stuff
2020-05-26 renamed target simulation to x86
2020-05-26 modified cmake file, apply objcopy only for main unit target
2020-05-26 refactored target mainunit for driver using
2020-05-31 added x86 debug build
2020-05-31 added googletest
2020-05-31 set googletest to version 1.10.0
2020-05-31 fixed false submodule version via .gitmodules
2020-08-30 removed folder Software, moved to own git repositories WomoLIN-Sw-..
2020-08-30 added pictures
2020-08-30 added pic powerled
2020-08-30 added pic controlled
2020-10-27 Fix VE direct bug in schematic
2020-10-28 Patch LIB mit Netzwerk Bauteilen, ESP32 und PY hinzu gefügt, PI Netzteil auf 5A
2020-11-09 Anbindung Raspberry Shield, ESP32 Netzwerk PHY forrtgesetzt
2020-11-16 ESP32 Netzwerk PHY und SD fertig, SD STM32 auf Micro SD, Womo_LIN Lib mit Micro SD gepatcht
2020-11-26 Fix LPUART RX TX vertauschung an PB10/11
2020-11-30 Board Placement V3.0 begonnen, ESP32 mit LAN platziert, Bluetooth Modul entfernt
2020-12-27 Display Unit Zusätzliche Buchsen Mini Fit für den Bus, Befestigung um 5mm verschoben, Bauteil Placement.
2020-12-29 Fehlende Teile gerouted
2020-12-29 Lengthmatch OctoSPI again Remove leftover traces General cleanup
2020-12-31 Problem Vermischung mit V1 Layoutdaten gefixt, Octo SPI Längenmatching. V3 Produktionsdaten für JCLPCB erzeugt.
2021-03-02 Add Truma Test Schematics
2021-03-16 Add CAN to ESP 32 and Raspberry (nicht fertig) diverse Fehlerkorrekturen.
2021-03-21 Weiter kleinere Anpassungen am CAN und Board
